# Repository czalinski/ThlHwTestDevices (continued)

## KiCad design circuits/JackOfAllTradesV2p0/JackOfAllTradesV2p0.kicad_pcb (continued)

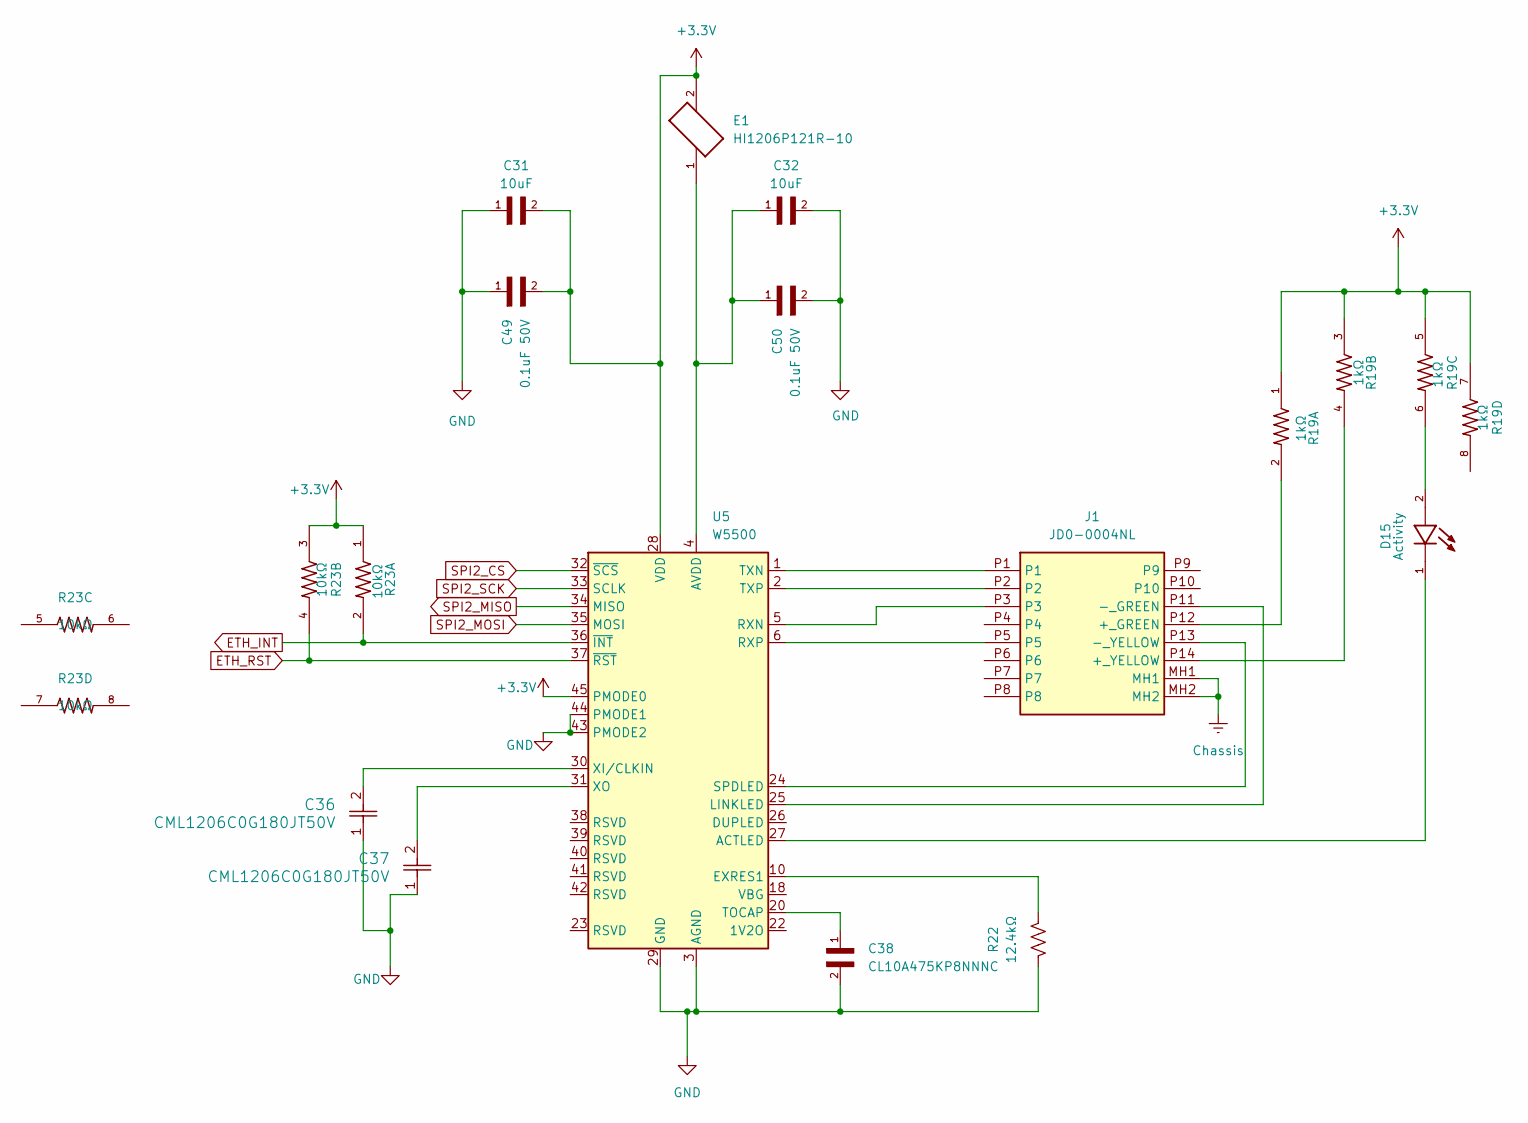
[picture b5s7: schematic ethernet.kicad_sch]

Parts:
C31, C32: 10uF; CAPC3216X180N
C36, C37: CML1206C0G180JT50V; CAP_CML_1206_.3-8200PF_STP
C38: CL10A475KP8NNNC; CAPC1608X90N
C49, C50: 0.1uF 50V; CAPC2012X70
D15: Activity; LED_LTST-C170GKT; PARTREV I
E1: HI1206P121R-10; FB_HI1206P121R-10
J1: JD0-0004NL; JD00004NL; Manufacturer_Part_Number JD0-0004NL; Mouser Part Number 673-JD0-0004NL
R19: 1kΩ; RESCAV80P320X160X70-8N
R22: 12.4kΩ; RES_1206
R23: 10kΩ; RESCAV80P320X160X70-8N
U5: W5500; LQFP-48_7x7mm_P0.5mm

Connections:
+3.3V: C31.2, C49.2, E1.2, R19.1, R19.3, R19.5, R19.7, R23.1, R23.3, U5.28 (VDD), U5.45 (PMODE0); also elsewhere on the board
Chassis: J1.MH1, J1.MH2; also elsewhere on the board
ETH_INT: R23.2, U5.36 (~INT); also elsewhere on the board
ETH_RST: R23.4, U5.37 (~RST); also elsewhere on the board
GND: C31.1, C32.2, C36.1, C37.1, C38.2, C49.1, C50.2, R22.2, U5.3 (AGND), U5.9 (AGND), U5.14 (AGND), U5.16 (AGND), U5.19 (AGND), U5.29 (GND), U5.43 (PMODE2), U5.44 (PMODE1), U5.48 (AGND); also elsewhere on the board
unnamed: C32.1, C50.1, E1.1, U5.4 (AVDD), U5.8 (AVDD), U5.11 (AVDD), U5.15 (AVDD), U5.17 (AVDD), U5.21 (AVDD)
unnamed: D15.2, R19.6
unnamed: J1.P12 (+_GREEN), R19.2
unnamed: J1.P14 (+_YELLOW), R19.4
unnamed: J1.P11 (-_GREEN), U5.25 (LINKLED)
unnamed: J1.P13 (-_YELLOW), U5.24 (SPDLED)
unnamed: D15.1, U5.27 (ACTLED)
unnamed: R22.1, U5.10 (EXRES1)
unnamed: J1.P3, U5.5 (RXN)
unnamed: J1.P5, U5.6 (RXP)
unnamed: C38.1, U5.20 (TOCAP)
unnamed: J1.P1, U5.1 (TXN)
unnamed: J1.P2, U5.2 (TXP)
unnamed: C36.2, U5.30 (XI/CLKIN)
unnamed: C37.2, U5.31 (XO)
SPI2_CS: U5.32 (~SCS); also elsewhere on the board
SPI2_MISO: U5.34 (MISO); also elsewhere on the board
SPI2_MOSI: U5.35 (MOSI); also elsewhere on the board
SPI2_SCK: U5.33 (SCLK); also elsewhere on the board

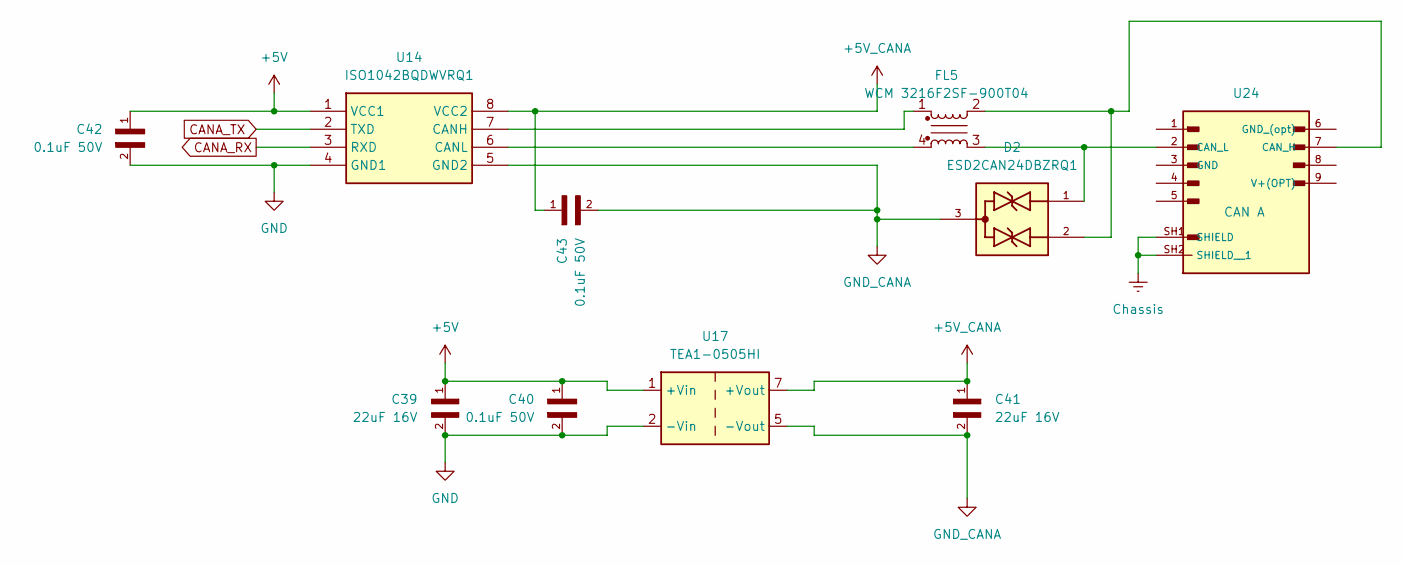
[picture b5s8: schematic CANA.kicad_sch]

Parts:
C39, C41: 22uF 16V; CAPC3216X95N
C40, C42, C43: 0.1uF 50V; CAPC2012X70
D2: ESD2CAN24DBZRQ1; SOT95P237X112-3N; PARTREV C
FL5: WCM 3216F2SF-900T04; WCM 3216F2SF-900T04-1206
U14: ISO1042BQDWVRQ1; SOIC127P1150X280-8N; Manufacturer_Part_Number ISO1042BQDWVRQ1; Mouser Part Number 595-ISO1042BQDWVRQ1
U17: TEA1-0505HI; Converter_DCDC_TRACO_TEA1-xxxxHI_THT
U24: CAN A; ASSMANN_A-DS_09_A_KG-T2S

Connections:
+5V: C39.1, C40.1, C42.1, U14.1 (VCC1), U17.1 (+Vin); also elsewhere on the board
+5V_CANA: C41.1, C43.1, U14.8 (VCC2), U17.7 (+Vout)
CANA_RX: U14.3 (RXD); also elsewhere on the board
CANA_TX: U14.2 (TXD); also elsewhere on the board
Chassis: U24.SH1 (SHIELD), U24.SH2 (SHIELD__1); also elsewhere on the board
GND: C39.2, C40.2, C42.2, U14.4 (GND1), U17.2 (-Vin); also elsewhere on the board
GND_CANA: C41.2, C43.2, D2.3, U14.5 (GND2), U17.5 (-Vout); also elsewhere on the board
unnamed: FL5.1, U14.7 (CANH)
unnamed: FL5.4, U14.6 (CANL)
unnamed: D2.2, FL5.2, U24.7 (CAN_H)
unnamed: D2.1, FL5.3, U24.2 (CAN_L)

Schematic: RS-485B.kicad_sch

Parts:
C16, C21: 22uF 16V; CAPC3216X95N
C17, C18, C22: 0.1uF 50V; CAPC2012X70
CR5: ESDA25-4BP6; SOT666_ESDA25_STM
FL1, FL2: WCM 3216F2SF-900T04; WCM 3216F2SF-900T04-1206
JP2: Term AB; PinHeader_1x02_P2.54mm_Vertical
JP3: Term YZ; PinHeader_1x02_P2.54mm_Vertical
R3, R4: 120Ω; RES_1206
U3: TEA1-0505HI; Converter_DCDC_TRACO_TEA1-xxxxHI_THT
U10: TPT7488-SOBR; SOBWSOP-16-A_TPK
U20: RS485 B; ASSMANN_A-DS_09_A_KG-T2S

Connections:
+5V: C16.1, C17.1, C22.1, U3.1 (+Vin), U10.1 (VCCA); also elsewhere on the board
+5V_RS485B: C18.2, C21.1, U3.7 (+Vout), U10.16 (VCCB)
Chassis: U20.SH1 (SHIELD), U20.SH2 (SHIELD__1); also elsewhere on the board
GND: C16.2, C17.2, C22.2, U3.2 (-Vin), U10.2 (GNDA), U10.8 (GNDA); also elsewhere on the board
GND_RS485B: C18.1, C21.2, CR5.2, CR5.5, U3.5 (-Vout), U10.9 (GNDB), U10.15 (GNDB), U20.5 (GND); also elsewhere on the board
unnamed: JP2.1 (A), R3.1
unnamed: FL1.4, JP2.2 (B), U10.13 (B)
unnamed: JP3.1 (A), R4.1
unnamed: FL2.1, JP3.2 (B), U10.11 (Y)
unnamed: FL1.1, R3.2, U10.14 (A)
unnamed: FL2.4, R4.2, U10.12 (Z)
unnamed: CR5.6, FL1.3, U20.4 (A)
unnamed: CR5.4, FL1.2, U20.3 (B)
unnamed: CR5.1, FL2.2, U20.2 (Y)
unnamed: CR5.3, FL2.3, U20.1 (Z)

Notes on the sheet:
RS-485 B

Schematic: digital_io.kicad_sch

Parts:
C15: 0.1uF 50V; CAPC2012X70
D18: G0; LED_LTST-C170GKT; PARTREV I
D19: G1; LED_LTST-C170GKT; PARTREV I
D20: G2; LED_LTST-C170GKT; PARTREV I
D21: G3; LED_LTST-C170GKT; PARTREV I
D22: RLY0; LED_LTST-C170GKT; PARTREV I
D23: RLY1; LED_LTST-C170GKT; PARTREV I
D24: RLY2; LED_LTST-C170GKT; PARTREV I
D25: RLY3; LED_LTST-C170GKT; PARTREV I
D26: G4; LED_LTST-C170GKT; PARTREV I
D27: G5; LED_LTST-C170GKT; PARTREV I
D28: G6; LED_LTST-C170GKT; PARTREV I
D29: G7; LED_LTST-C170GKT; PARTREV I
D30: RLY4; LED_LTST-C170GKT; PARTREV I
D31: RLY5; LED_LTST-C170GKT; PARTREV I
D32: RLY6; LED_LTST-C170GKT; PARTREV I
D33: RLY7; LED_LTST-C170GKT; PARTREV I
J3: GPIO 4-7; CONN_1989803_PXC
J4: Relay 0-3; CONN_1989803_PXC
J5: Relay 4-7; CONN_1989803_PXC
J6: GPIO 0-3; CONN_1989803_PXC
RN5, RN6, RN7, RN8: 2.2kΩ; RESCAXS50P200X100X55-8N
U7: ULN2803A; SOIC-18W_7.5x11.6mm_P1.27mm
U8: MCP23017T-E_SO; SOIC127P1030X265-28N

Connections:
+3.3V: C15.1, U8.9 (VDD); also elsewhere on the board
+VDC: U7.10 (COM); also elsewhere on the board
GND: C15.2, D18.1, D19.1, D20.1, D21.1, D22.1, D23.1, D24.1, D25.1, D26.1, D27.1, D28.1, D29.1, D30.1, D31.1, D32.1, D33.1, J3.2, J3.4, J3.6, J3.8, J4.2, J4.4, J4.6, J4.8, J5.2, J5.4, J5.6, J5.8, J6.2, J6.4, J6.6, J6.8, U7.9 (GND), U8.10 (VSS), U8.15 (A0), U8.16 (A1), U8.17 (A2); also elsewhere on the board
I2C1_SCL: U8.12 (SCK); also elsewhere on the board
I2C1_SDA: U8.13 (SDA); also elsewhere on the board
unnamed: D18.2, RN5.1
unnamed: D19.2, RN5.3
unnamed: D20.2, RN5.5
unnamed: D21.2, RN5.7
unnamed: D22.2, RN6.1
unnamed: D23.2, RN6.3
unnamed: D24.2, RN6.5
unnamed: D25.2, RN6.7
unnamed: D26.2, RN7.1
unnamed: D27.2, RN7.3
unnamed: D28.2, RN7.5
unnamed: D29.2, RN7.7
unnamed: D30.2, RN8.1
unnamed: D31.2, RN8.3
unnamed: D32.2, RN8.5
unnamed: D33.2, RN8.7
unnamed: RN8.8, U7.1 (IN1), U8.28 (GPA7)
unnamed: RN8.6, U7.2 (IN2), U8.27 (GPA6)
unnamed: RN8.4, U7.3 (IN3), U8.26 (GPA5)
unnamed: RN8.2, U7.4 (IN4), U8.25 (GPA4)
unnamed: RN6.8, U7.5 (IN5), U8.24 (GPA3)
unnamed: RN6.6, U7.6 (IN6), U8.23 (GPA2)
unnamed: RN6.4, U7.7 (IN7), U8.22 (GPA1)
unnamed: RN6.2, U7.8 (IN8), U8.21 (GPA0)
unnamed: J5.7, U7.18 (OUT1)
unnamed: J5.5, U7.17 (OUT2)
unnamed: J5.3, U7.16 (OUT3)
unnamed: J5.1, U7.15 (OUT4)
unnamed: J4.7, U7.14 (OUT5)
unnamed: J4.5, U7.13 (OUT6)
unnamed: J4.3, U7.12 (OUT7)
unnamed: J4.1, U7.11 (OUT8)
unnamed: J6.1, RN5.2, U8.1 (GPB0)
unnamed: J6.3, RN5.4, U8.2 (GPB1)
unnamed: J6.5, RN5.6, U8.3 (GPB2)
unnamed: J6.7, RN5.8, U8.4 (GPB3)
unnamed: J3.1, RN7.2, U8.5 (GPB4)
unnamed: J3.3, RN7.4, U8.6 (GPB5)
unnamed: J3.5, RN7.6, U8.7 (GPB6)
unnamed: J3.7, RN7.8, U8.8 (GPB7)

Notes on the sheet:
I2C: 0x20
Communication Status

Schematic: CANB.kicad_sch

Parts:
C44, C46, C47: 0.1uF 50V; CAPC2012X70
C45, C48: 22uF 16V; CAPC3216X95N
D11: ESD2CAN24DBZRQ1; SOT95P237X112-3N; PARTREV C
FL6: WCM 3216F2SF-900T04; WCM 3216F2SF-900T04-1206
U15: ISO1042BQDWVRQ1; SOIC127P1150X280-8N; Manufacturer_Part_Number ISO1042BQDWVRQ1; Mouser Part Number 595-ISO1042BQDWVRQ1
U22: TEA1-0505HI; Converter_DCDC_TRACO_TEA1-xxxxHI_THT
U25: CAN B; ASSMANN_A-DS_09_A_KG-T2S

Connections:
+5V: C44.1, C45.1, C46.1, U15.1 (VCC1), U22.1 (+Vin); also elsewhere on the board
+5V_CANB: C47.1, C48.1, U15.8 (VCC2), U22.7 (+Vout)
CANB_RX: U15.3 (RXD); also elsewhere on the board
CANB_TX: U15.2 (TXD); also elsewhere on the board
Chassis: U25.SH1 (SHIELD), U25.SH2 (SHIELD__1); also elsewhere on the board
GND: C44.2, C45.2, C46.2, U15.4 (GND1), U22.2 (-Vin); also elsewhere on the board
GND_CANA: C47.2, D11.3, U15.5 (GND2); also elsewhere on the board
GND_CANB: C48.2, U22.5 (-Vout)
unnamed: FL6.1, U15.7 (CANH)
unnamed: FL6.4, U15.6 (CANL)
unnamed: D11.2, FL6.2, U25.7 (CAN_H)
unnamed: D11.1, FL6.3, U25.2 (CAN_L)

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
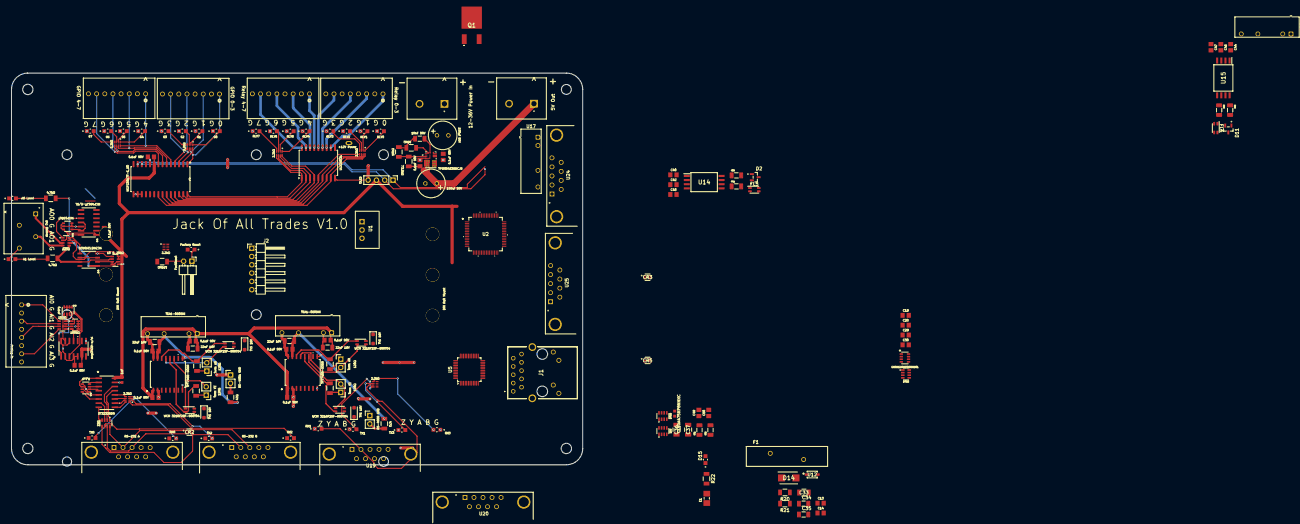
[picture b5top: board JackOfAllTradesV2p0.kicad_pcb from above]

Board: 2 copper layers, 175.0 x 120.0 mm, 170 parts (0 on the bottom side), 182 nets.

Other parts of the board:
D1, D2#2, D11#2, D12: TVS 16V; D_SOD-123F
JP4: RS-485B GND; PinHeader_1x02_P2.54mm_Vertical
JP7: RS-485A GND; PinHeader_1x02_P2.54mm_Vertical
R5, R11: 47Ω; RES_1206
TP4: +12V Power; KEYSTONE_4954_Slot

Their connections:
GND: JP4.1 (A), JP7.1 (A); also elsewhere on the board
GND_RS485A: R11.1; also elsewhere on the board
GND_RS485B: R5.1; also elsewhere on the board
unnamed: JP4.2 (B), R5.2
unnamed: JP7.2 (B), R11.2

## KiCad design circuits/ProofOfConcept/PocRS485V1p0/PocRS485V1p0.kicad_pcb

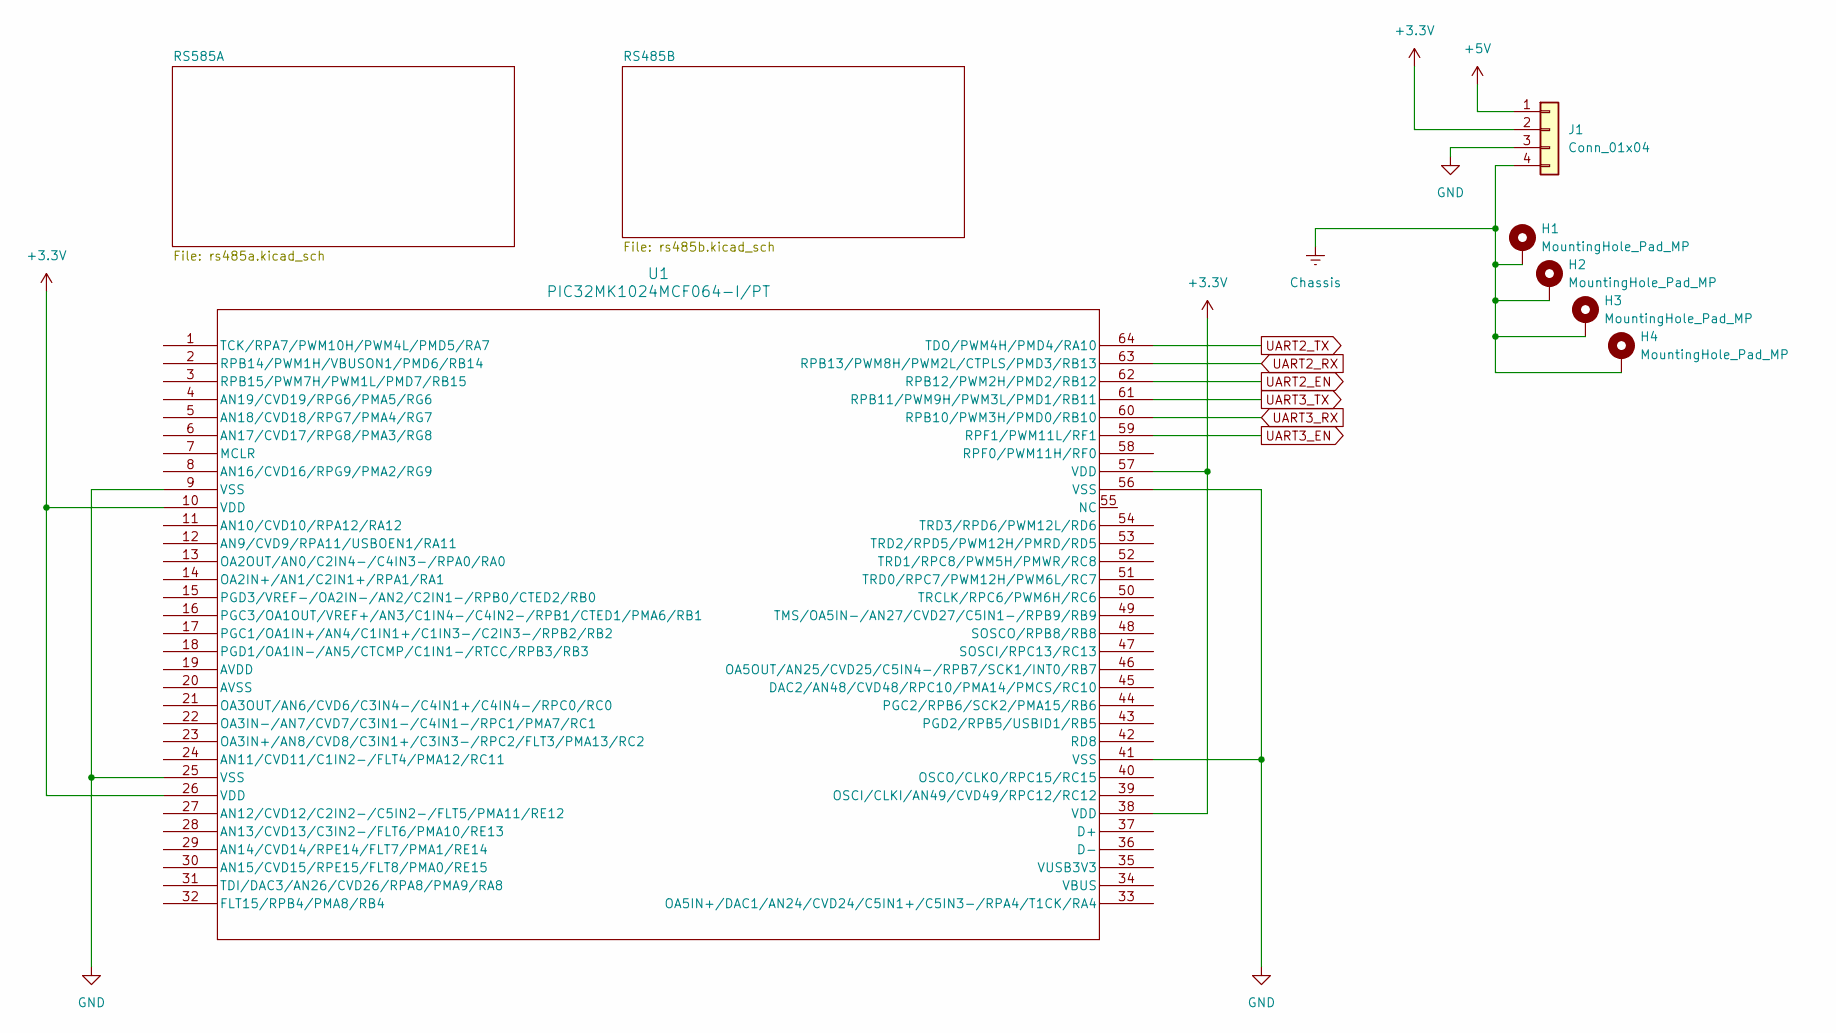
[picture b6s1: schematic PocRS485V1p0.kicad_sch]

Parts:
H1, H2, H3, H4: MountingHole_Pad_MP; MountingHole_3.2mm_M3_Pad_Via
J1: Conn_01x04; PinHeader_1x04_P2.54mm_Vertical
U1: PIC32MK1024MCF064-I/PT; PIC64_Breakout

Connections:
+3.3V: J1.2, U1.10 (VDD), U1.26 (VDD), U1.38 (VDD), U1.57 (VDD)
+5V: J1.1; also elsewhere on the board
Chassis: H1.1 (MP_1), H2.1 (MP_1), H3.1 (MP_1), H4.1 (MP_1), J1.4; also elsewhere on the board
GND: J1.3, U1.9 (VSS), U1.25 (VSS), U1.41 (VSS), U1.56 (VSS); also elsewhere on the board
UART2_EN: U1.62 (RPB12/PWM2H/PMD2/RB12); also elsewhere on the board
UART2_RX: U1.63 (RPB13/PWM8H/PWM2L/CTPLS/PMD3/RB13); also elsewhere on the board
UART2_TX: U1.64 (TDO/PWM4H/PMD4/RA10); also elsewhere on the board
UART3_EN: U1.59 (RPF1/PWM11L/RF1); also elsewhere on the board
UART3_RX: U1.60 (RPB10/PWM3H/PMD0/RB10); also elsewhere on the board
UART3_TX: U1.61 (RPB11/PWM9H/PWM3L/PMD1/RB11); also elsewhere on the board

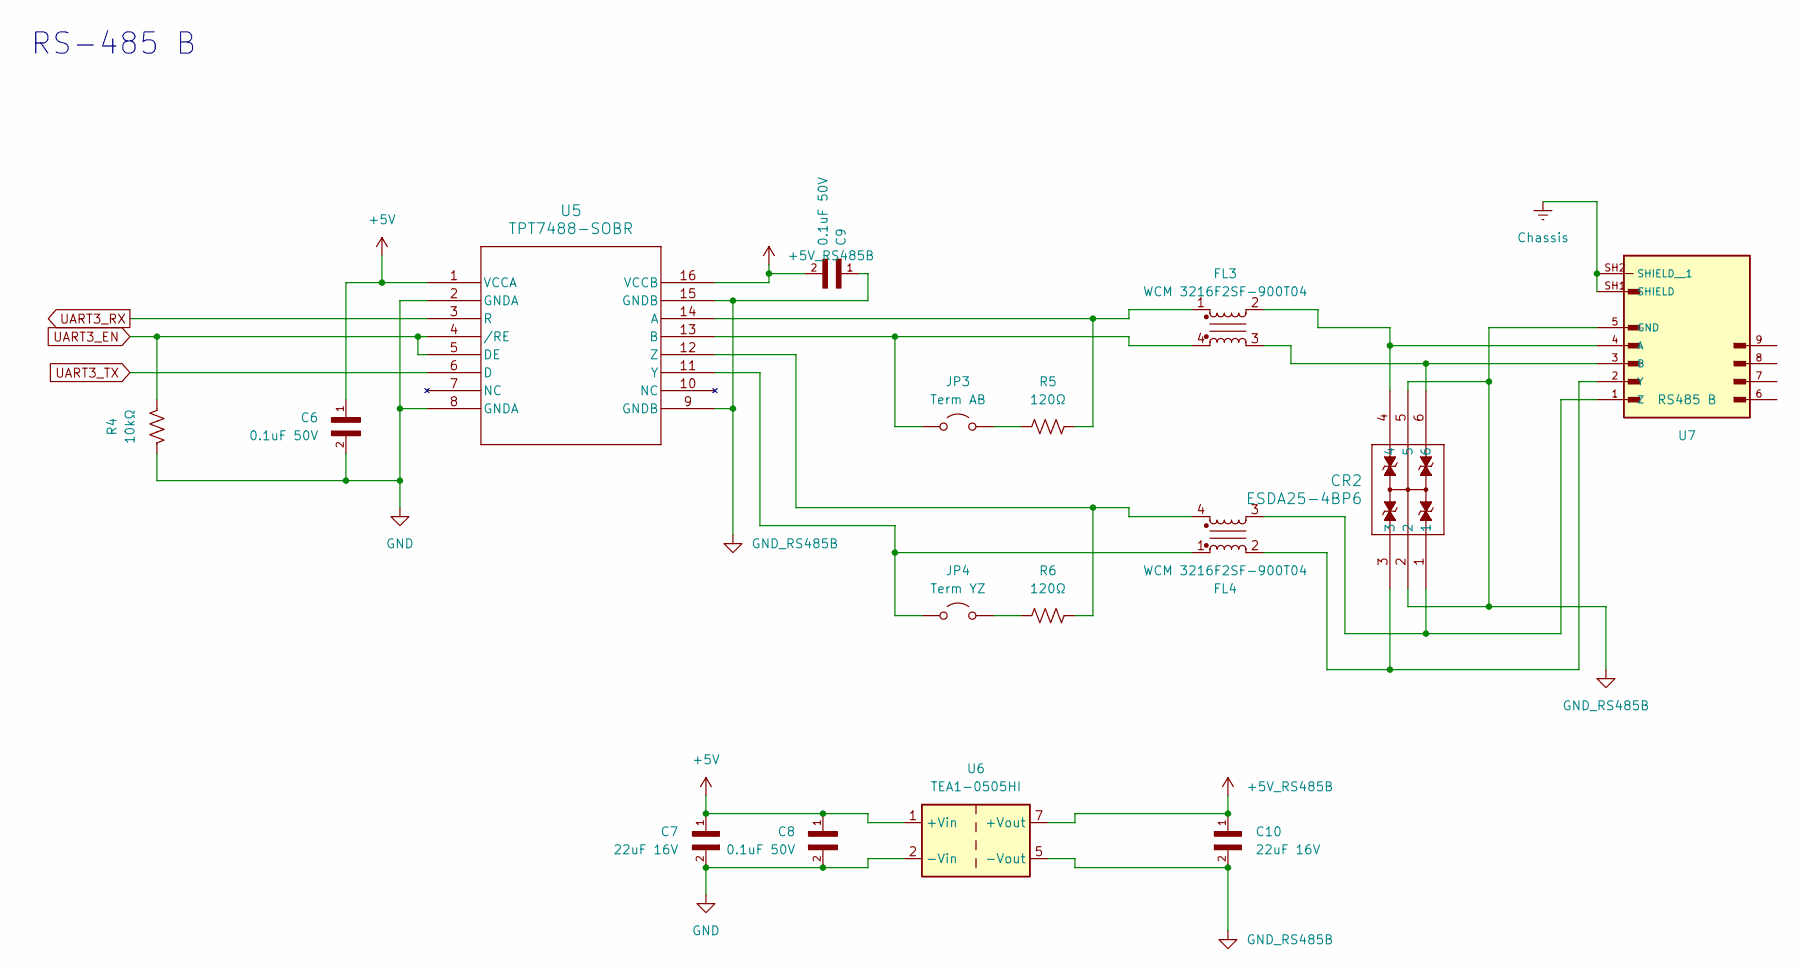
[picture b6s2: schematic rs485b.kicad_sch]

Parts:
C6, C8, C9: 0.1uF 50V; CAPC2012X70
C7, C10: 22uF 16V; CAPC3216X95N
CR2: ESDA25-4BP6; SOT666_ESDA25_STM
FL3, FL4: WCM 3216F2SF-900T04; WCM 3216F2SF-900T04-1206
JP3: Term AB; PinHeader_1x02_P2.54mm_Vertical
JP4: Term YZ; PinHeader_1x02_P2.54mm_Vertical
R4: 10kΩ; RES_1206
R5, R6: 120Ω; RES_1206
U5: TPT7488-SOBR; SOBWSOP-16-A_TPK
U6: TEA1-0505HI; Converter_DCDC_TRACO_TEA1-xxxxHI_THT
U7: RS485 B; ASSMANN_A-DS_09_A_KG-T2S

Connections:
+5V: C6.1, C7.1, C8.1, U5.1 (VCCA), U6.1 (+Vin); also elsewhere on the board
+5V_RS485B: C9.2, C10.1, U5.16 (VCCB), U6.7 (+Vout)
Chassis: U7.SH1 (SHIELD), U7.SH2 (SHIELD__1); also elsewhere on the board
GND: C6.2, C7.2, C8.2, R4.2, U5.2 (GNDA), U5.8 (GNDA), U6.2 (-Vin); also elsewhere on the board
GND_RS485B: C9.1, C10.2, CR2.2, CR2.5, U5.9 (GNDB), U5.15 (GNDB), U6.5 (-Vout), U7.5 (GND)
unnamed: JP3.1 (A), R5.1
unnamed: FL3.4, JP3.2 (B), U5.13 (B)
unnamed: JP4.1 (A), R6.1
unnamed: FL4.1, JP4.2 (B), U5.11 (Y)
unnamed: FL3.1, R5.2, U5.14 (A)
unnamed: FL4.4, R6.2, U5.12 (Z)
unnamed: CR2.4, FL3.2, U7.4 (A)
unnamed: CR2.6, FL3.3, U7.3 (B)
unnamed: CR2.3, FL4.2, U7.2 (Y)
unnamed: CR2.1, FL4.3, U7.1 (Z)
UART3_EN: R4.1, U5.4 (/RE), U5.5 (DE); also elsewhere on the board
UART3_RX: U5.3 (R); also elsewhere on the board
UART3_TX: U5.6 (D); also elsewhere on the board

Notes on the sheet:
RS-485 B

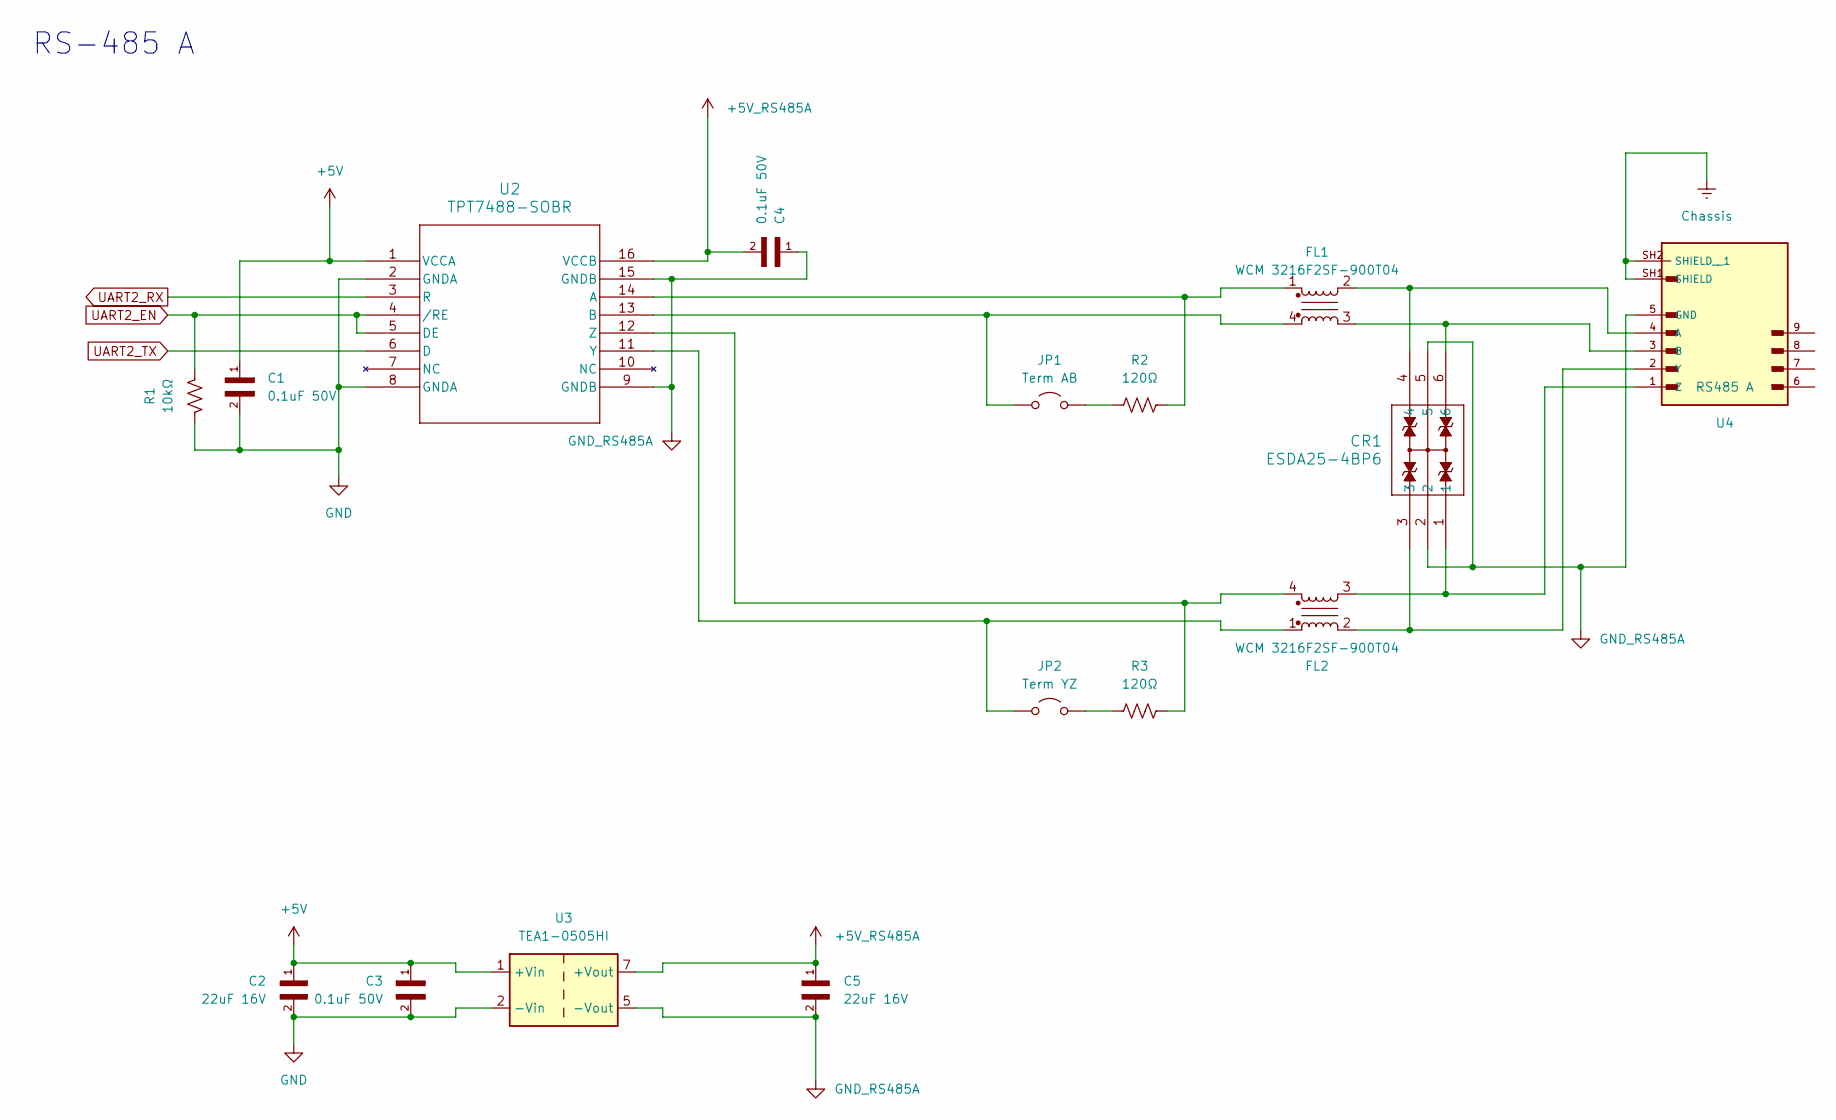
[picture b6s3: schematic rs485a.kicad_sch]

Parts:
C1, C3, C4: 0.1uF 50V; CAPC2012X70
C2, C5: 22uF 16V; CAPC3216X95N
CR1: ESDA25-4BP6; SOT666_ESDA25_STM
FL1, FL2: WCM 3216F2SF-900T04; WCM 3216F2SF-900T04-1206
JP1: Term AB; PinHeader_1x02_P2.54mm_Vertical
JP2: Term YZ; PinHeader_1x02_P2.54mm_Vertical
R1: 10kΩ; RES_1206
R2, R3: 120Ω; RES_1206
U2: TPT7488-SOBR; SOBWSOP-16-A_TPK
U3: TEA1-0505HI; Converter_DCDC_TRACO_TEA1-xxxxHI_THT
U4: RS485 A; ASSMANN_A-DS_09_A_KG-T2S

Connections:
+5V: C1.1, C2.1, C3.1, U2.1 (VCCA), U3.1 (+Vin); also elsewhere on the board
+5V_RS485A: C4.2, C5.1, U2.16 (VCCB), U3.7 (+Vout)
Chassis: U4.SH1 (SHIELD), U4.SH2 (SHIELD__1); also elsewhere on the board
GND: C1.2, C2.2, C3.2, R1.2, U2.2 (GNDA), U2.8 (GNDA), U3.2 (-Vin); also elsewhere on the board
GND_RS485A: C4.1, C5.2, CR1.2, CR1.5, U2.9 (GNDB), U2.15 (GNDB), U3.5 (-Vout), U4.5 (GND)
unnamed: JP1.1 (A), R2.1
unnamed: FL1.4, JP1.2 (B), U2.13 (B)
unnamed: JP2.1 (A), R3.1
unnamed: FL2.1, JP2.2 (B), U2.11 (Y)
unnamed: FL1.1, R2.2, U2.14 (A)
unnamed: FL2.4, R3.2, U2.12 (Z)
unnamed: CR1.4, FL1.2, U4.4 (A)
unnamed: CR1.6, FL1.3, U4.3 (B)
unnamed: CR1.3, FL2.2, U4.2 (Y)
unnamed: CR1.1, FL2.3, U4.1 (Z)
UART2_EN: R1.1, U2.4 (/RE), U2.5 (DE); also elsewhere on the board
UART2_RX: U2.3 (R); also elsewhere on the board
UART2_TX: U2.6 (D); also elsewhere on the board

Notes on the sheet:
RS-485 A

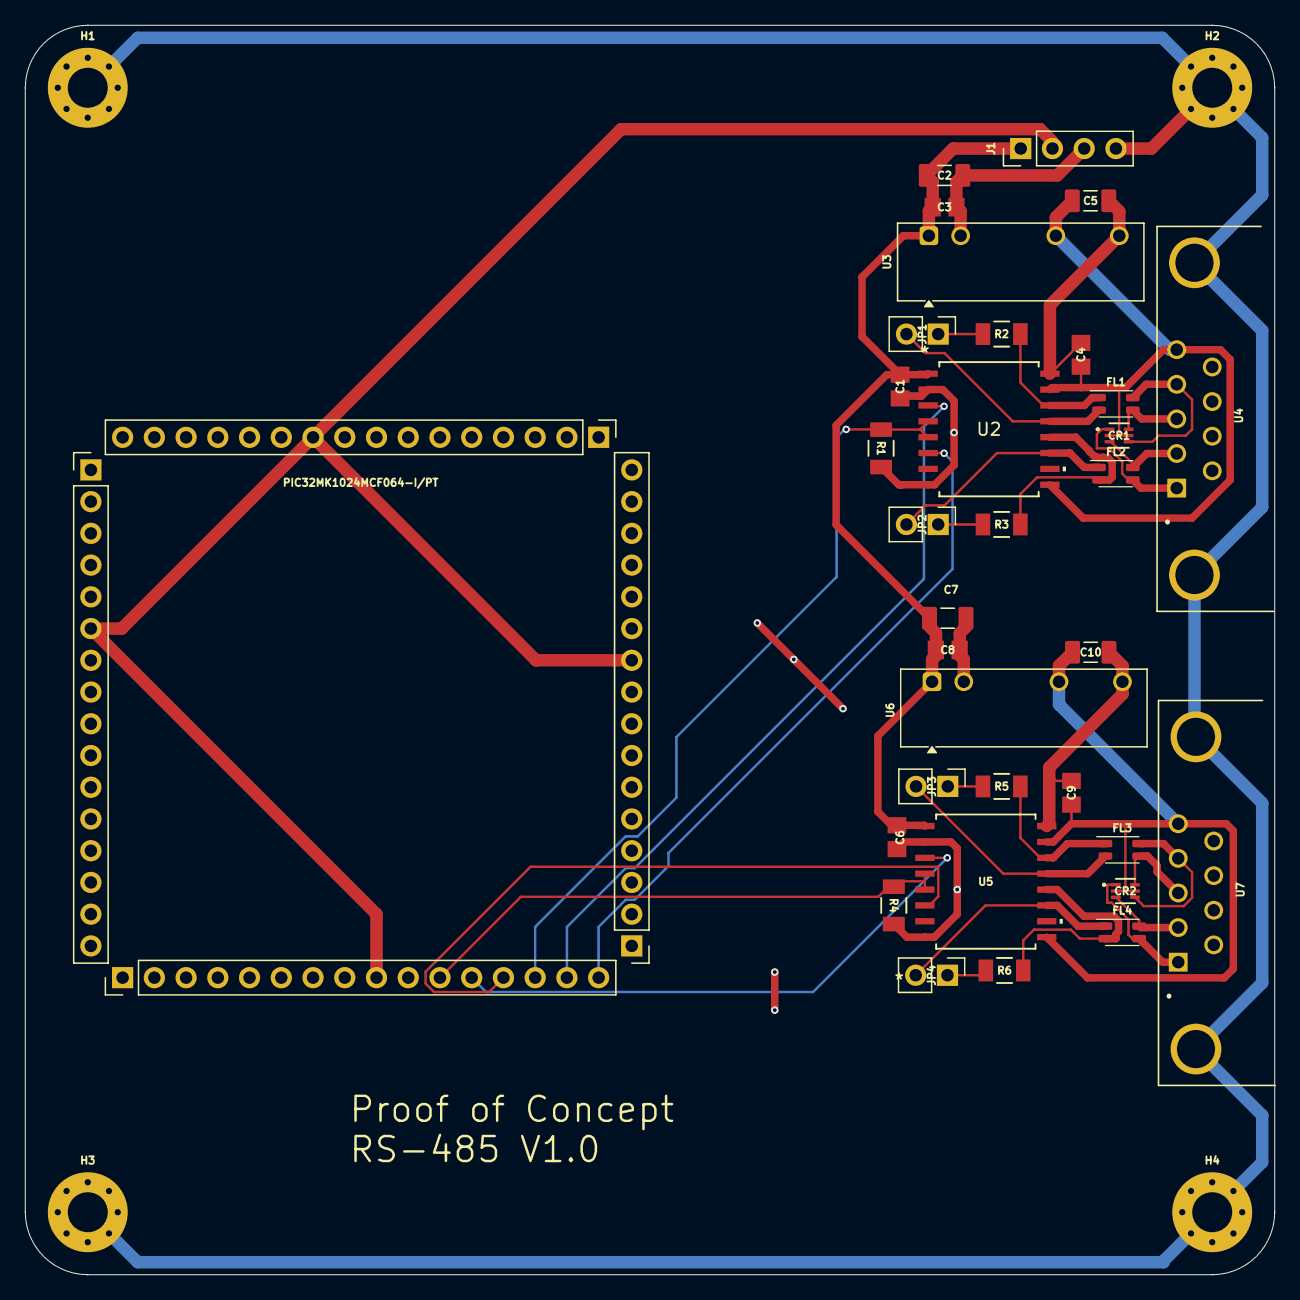
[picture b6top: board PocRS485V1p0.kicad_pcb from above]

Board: 2 copper layers, 100.0 x 100.0 mm, 38 parts (0 on the bottom side), 34 nets.

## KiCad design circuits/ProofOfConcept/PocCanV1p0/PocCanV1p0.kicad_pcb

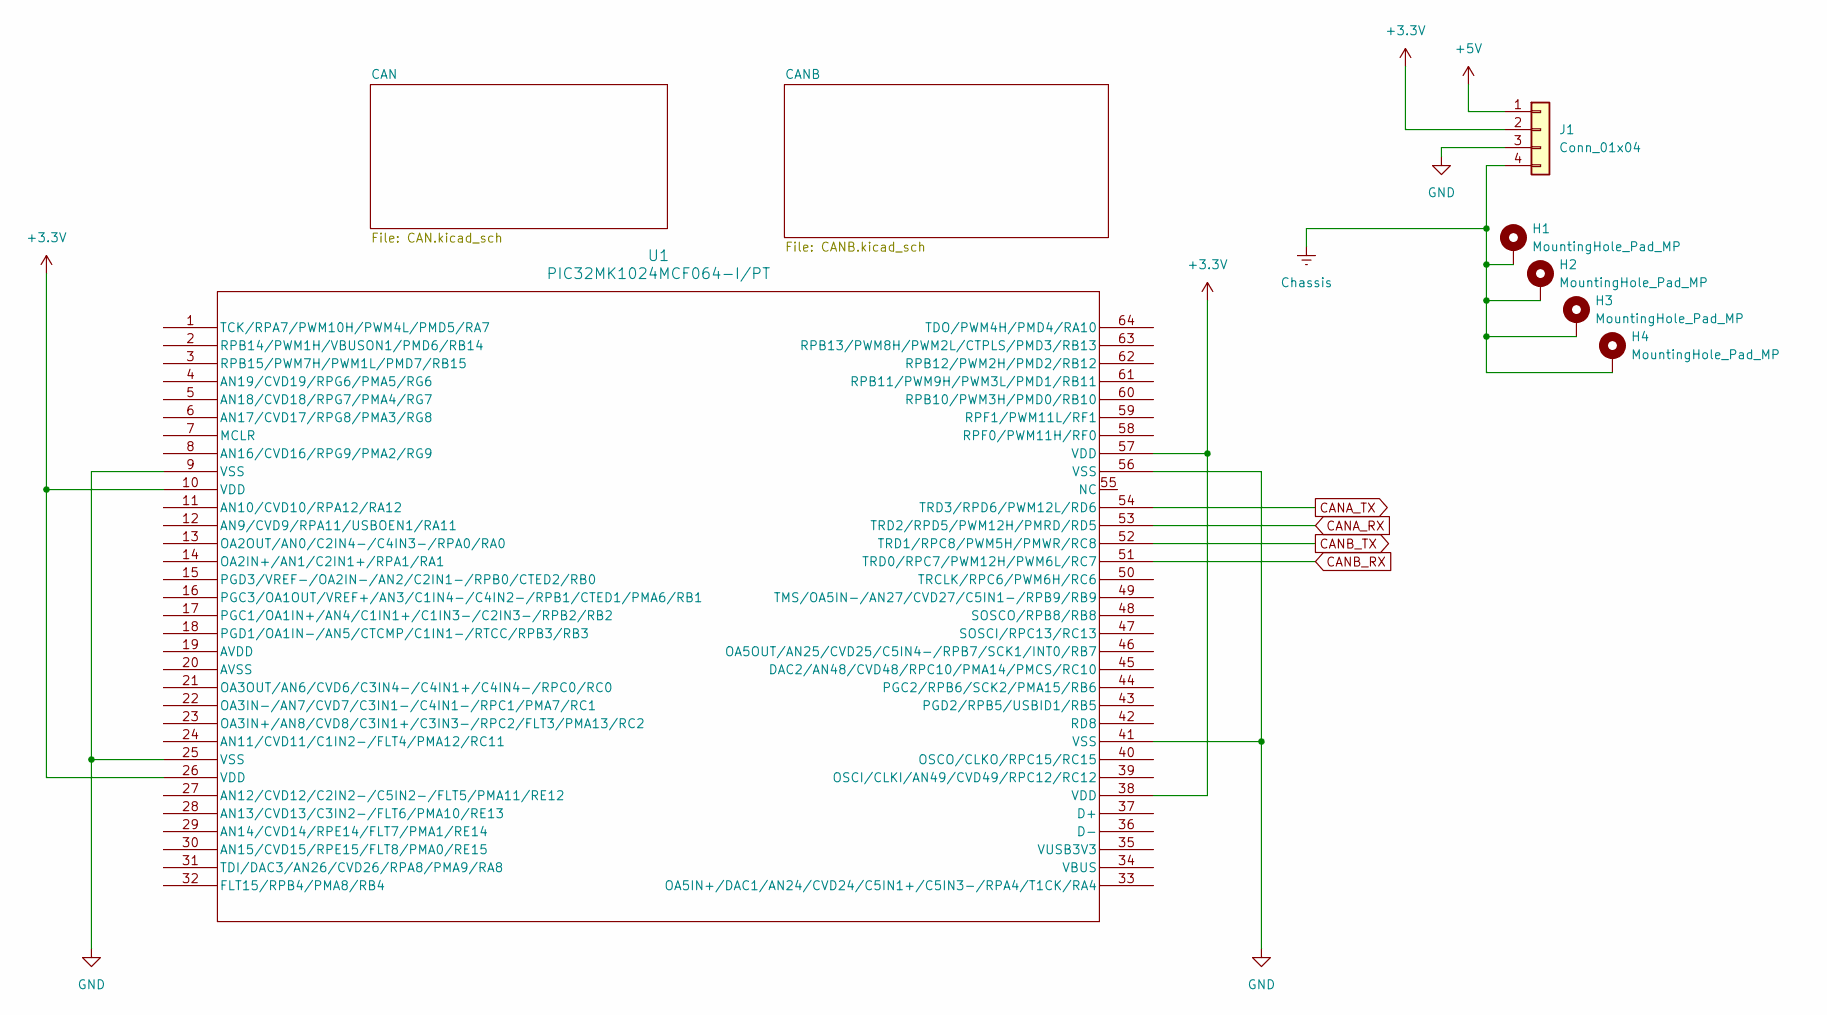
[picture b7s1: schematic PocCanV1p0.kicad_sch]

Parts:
H1, H2, H3, H4: MountingHole_Pad_MP; MountingHole_3.2mm_M3_Pad_Via
J1: Conn_01x04; PinHeader_1x04_P2.54mm_Vertical
U1: PIC32MK1024MCF064-I/PT; PIC64_Breakout

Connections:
+3.3V: J1.2, U1.10 (VDD), U1.26 (VDD), U1.38 (VDD), U1.57 (VDD)
+5V: J1.1; also elsewhere on the board
CANA_RX: U1.53 (TRD2/RPD5/PWM12H/PMRD/RD5); also elsewhere on the board
CANA_TX: U1.54 (TRD3/RPD6/PWM12L/RD6); also elsewhere on the board
CANB_RX: U1.51 (TRD0/RPC7/PWM12H/PWM6L/RC7); also elsewhere on the board
CANB_TX: U1.52 (TRD1/RPC8/PWM5H/PMWR/RC8); also elsewhere on the board
Chassis: H1.1 (MP_1), H2.1 (MP_1), H3.1 (MP_1), H4.1 (MP_1), J1.4; also elsewhere on the board
GND: J1.3, U1.9 (VSS), U1.25 (VSS), U1.41 (VSS), U1.56 (VSS); also elsewhere on the board

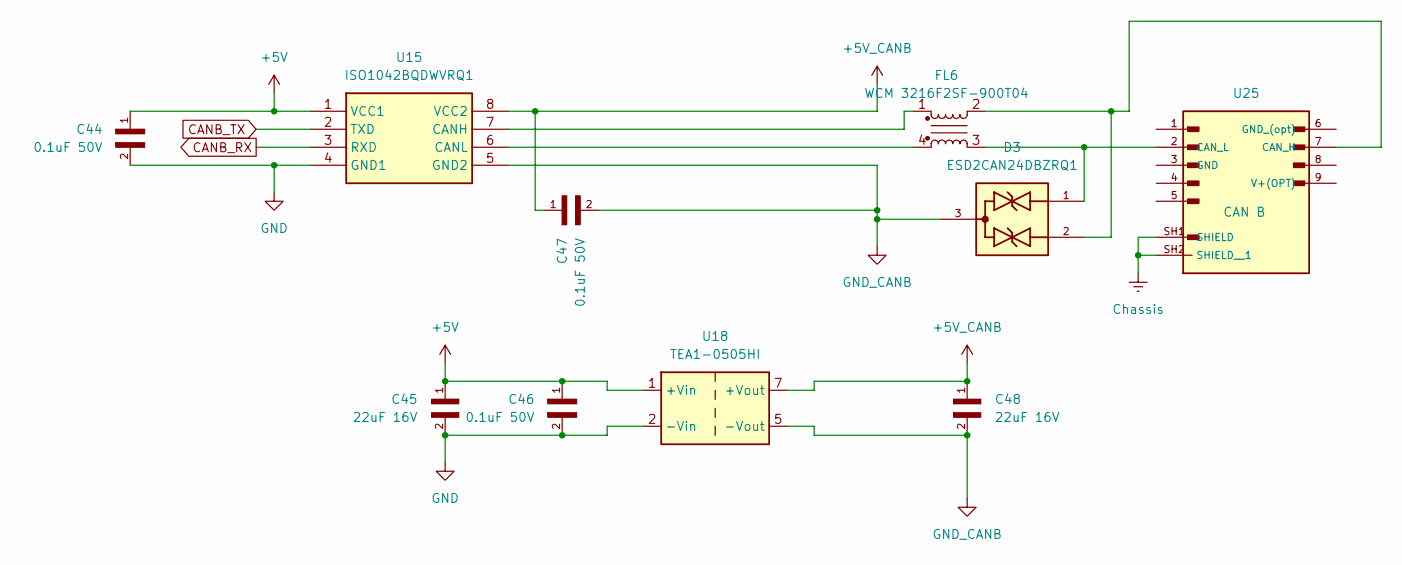
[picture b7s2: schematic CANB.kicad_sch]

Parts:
C44, C46, C47: 0.1uF 50V; CAPC2012X70
C45, C48: 22uF 16V; CAPC3216X95N
D3: ESD2CAN24DBZRQ1; SOT95P237X112-3N; PARTREV C
FL6: WCM 3216F2SF-900T04; WCM 3216F2SF-900T04-1206
U15: ISO1042BQDWVRQ1; SOIC127P1150X280-8N; Manufacturer_Part_Number ISO1042BQDWVRQ1; Mouser Part Number 595-ISO1042BQDWVRQ1
U18: TEA1-0505HI; Converter_DCDC_TRACO_TEA1-xxxxHI_THT
U25: CAN B; ASSMANN_A-DS_09_A_KG-T2S

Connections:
+5V: C44.1, C45.1, C46.1, U15.1 (VCC1), U18.1 (+Vin); also elsewhere on the board
+5V_CANB: C47.1, C48.1, U15.8 (VCC2), U18.7 (+Vout)
CANB_RX: U15.3 (RXD); also elsewhere on the board
CANB_TX: U15.2 (TXD); also elsewhere on the board
Chassis: U25.SH1 (SHIELD), U25.SH2 (SHIELD__1); also elsewhere on the board
GND: C44.2, C45.2, C46.2, U15.4 (GND1), U18.2 (-Vin); also elsewhere on the board
GND_CANB: C47.2, C48.2, D3.3, U15.5 (GND2), U18.5 (-Vout)
unnamed: FL6.1, U15.7 (CANH)
unnamed: FL6.4, U15.6 (CANL)
unnamed: D3.2, FL6.2, U25.7 (CAN_H)
unnamed: D3.1, FL6.3, U25.2 (CAN_L)
